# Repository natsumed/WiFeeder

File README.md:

# WiFeeder v2 — Project README

> **Wireless Automatic Cow Feeding System**  
> NRF24L01+ 2.4 GHz Communication | NUCLEO-L432KC | Raspberry Pi  

> **Status (2026-08-11):** Wiring MVP locked (PCA9685). **NRF VCC = 3.3 V** — Nucleo 5V (~4.8 V) permanently kills PA/LNA (SPI can still look OK). Firmware motor path is I2C PCA9685. Actuator hybrid PCB in [`pcb/`](pcb/). Pi host uses **JSON**. RF over-air still the bring-up gate (need **new** modules after the 5 V damage).

---

## Quick Navigation

| Document | Description |
|----------|-------------|
| [docs/wifeeder-v2-final-plan.md](./docs/wifeeder-v2-final-plan.md) | **Implementation plan** — pins, v1 port, phases, acceptance |
| [ARCHITECTURE.md](./ARCHITECTURE.md) | System architecture, state machines, data flow diagrams |
| [HARDWARE.md](./HARDWARE.md) | Pin mappings, wiring diagrams, power budget |
| [pcb/](./pcb/) | **Actuator hybrid PCB** (KiCad **6.0**) — PCA9685 + bucks on-board; Nucleo/IBT/NRF modules |
| [wiring/](./wiring/) | **Fritzing pack** — bench / no-PCB; `wifeeder-v2.fzz`, GX map |
| [PROTOCOL.md](./PROTOCOL.md) | NRF24L01+ communication protocol specification |
| [SOFTWARE.md](./SOFTWARE.md) | Code architecture, task model, class diagrams |
| [TESTING.md](./TESTING.md) | Test strategy, test cases, validation procedures |
| [DEPLOYMENT.md](./DEPLOYMENT.md) | Build, flash, and deployment instructions |
| [TROUBLESHOOTING.md](./TROUBLESHOOTING.md) | Common problems and solutions |
| [BILL_OF_MATERIALS.md](./BILL_OF_MATERIALS.md) | Complete materials list |

---

## System Overview

```mermaid
graph LR
    CLOUD[" Agpro Cloud"] <-->|"MQTT"| RPI[" Raspberry Pi"]
    RPI <-.->|"NRF24L01+<br/>2.4 GHz"| STM[" NUCLEO-L432KC"]
    STM --> RFID[" RFID Reader"]
    STM --> MOTOR[" Motors (2x)"]
    STM --> HX711[" Load Cell"]
```

WiFeeder v2 is a complete rewrite of the original CAN-bus-based cow feeding system, replacing the problematic wired communication with reliable NRF24L01+ wireless modules.

- **Cow approaches feeder** → RFID tag read
- **Tag sent over NRF24L01+** → Raspberry Pi controller
- **Diet calculation** → Feed command sent back
- **Motors dispense feed** → Encoders verify quantity
- **Consumption reported** → Agpro cloud via MQTT

---

## Repository Structure

```
wifeeder-v2/
├── README.md                          # This file
├── ARCHITECTURE.md                    # System architecture
├── HARDWARE.md                        # Hardware specs
├── PROTOCOL.md                        # Communication protocol
├── SOFTWARE.md                        # Software architecture
├── TESTING.md                         # Test plan
├── DEPLOYMENT.md                      # Deployment guide
├── TROUBLESHOOTING.md                 # Troubleshooting
├── BILL_OF_MATERIALS.md              # Materials list
│
├── stm32/                             # STM32 firmware
│   ├── Core/{Inc,Src}/               # Application code
│   ├── Drivers/                       # HAL & CMSIS
│   ├── Middlewares/                   # FreeRTOS
│   └── Config/                        # RTOS config
│
├── raspberry/                         # RPi host software
│   ├── src/                           # C++ source
│   ├── include/                       # C++ headers
│   ├── config/                        # JSON configs
│   └── tests/                         # GTest tests
│
├── pcb/                               # Actuator hybrid KiCad 8 carrier
├── wiring/                            # Fritzing bench pack
├── docs/                              # Additional docs
├── scripts/                           # Build & deploy
├── tests/                             # Integration tests
└── assets/                            # Images & diagrams
```

---

## Key Differences from v1

| Feature | v1 (CAN) | v2 (NRF24L01+) |
|---------|----------|-----------------|
| Communication | CAN bus (wired) | NRF24L01+ (wireless) |
| MCU | STM32L486ZGTx | NUCLEO-L432KC |
| Motor Driver | GTK08 | IBT-2 (BTS7960B) |
| Power | Direct 12V | Mini360 DC-DC Buck |
| Protocol | CAN frames (8B) | NRF packets (32B) |
| Database | JSON file (`wifeeder-data.json`) | SQLite (planned) |
| Range | Limited by cable | ~100m wireless |
| Cost per node | ~$15 (CAN parts) | ~$3 (NRF module) |

---

## Quick Start

### Prerequisites

- **Hardware**: NUCLEO-L432KC, NRF24L01+ x2, IBT-2, RFID reader, motors with encoders, Raspberry Pi
- **Software**: STM32CubeIDE, CMake 3.16+, GCC arm-none-eabi, g++ C++20
- **Pi Tools**: spidev / sysfs GPIO, libmosquitto (optional), JSON file DB

### Build STM32 Firmware

```bash
cd stm32
mkdir build && cd build
cmake .. -DCMAKE_TOOLCHAIN_FILE=../cmake/toolchain-arm-none-eabi.cmake
cmake --build . -j$(nproc)
# Flash: Connect Nucleo via USB, drag .bin to virtual drive
```

### Build Raspberry Pi Host

```bash
cd raspberry
mkdir build && cd build
cmake .. -DCMAKE_BUILD_TYPE=Release
cmake --build . -j$(nproc)
# Install: sudo cmake --install .
```

### Configure & Run

```bash
# On Pi:
sudo systemctl enable wifeeder-v2
sudo systemctl start wifeeder-v2

# Monitor:
journalctl -u wifeeder-v2 -f

# Check NRF communication:
sudo candump nrf  # (uses virtual CAN interface to monitor NRF messages)
```

---

## Communication Flow

```mermaid
sequenceDiagram
    participant Cow as 
    participant STM32 as STM32
    participant RPi as RPi
    participant Cloud as  Cloud

    loop Every 5s
        STM32->>RPi: STATUS (heartbeat)
        RPi->>STM32: ACK
    end

    Cow->>STM32: RFID tag read
    STM32->>RPi: RFID_TAG
    RPi->>RPi: Lookup diet
    RPi->>STM32: FEED_CMD (revolutions)
    STM32->>STM32: Dispense feed
    STM32->>RPi: FEED_DONE (actual)
    RPi->>Cloud: Publish via MQTT
```

---

## License

Proprietary — CodinTek © 2024

## Support

For questions or issues, see [TROUBLESHOOTING.md](./TROUBLESHOOTING.md) or contact the development team.

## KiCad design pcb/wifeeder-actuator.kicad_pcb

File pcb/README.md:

# WiFeeder actuator carrier (hybrid, spin 1)

KiCad **6.0** project (matches this machine): [`wifeeder-actuator.kicad_pro`](wifeeder-actuator.kicad_pro)

Replaces the Fritzing breadboard, PCA9685 breakout, Mini360, and jumper harness.
Firmware pins are unchanged — see [`../stm32/Core/Inc/board.h`](../stm32/Core/Inc/board.h) and
[`../wiring/CONNECTOR_MAP.md`](../wiring/CONNECTOR_MAP.md).

| On this PCB | Plug-in modules | Off-board |
|-------------|-----------------|-----------|
| PCA9685 + passives | NUCLEO-L432KC | Raspberry Pi + NRF |
| Fixed 5 V + 3.3 V bucks | IBT-2 (BTS7960) | PN01007BRKT + GTS06 |
| Enc / I2C pull-ups, fuse, TVS, P-FET | NRF24 + AM1117 (2×4) | 12 V pack |
| Screw / JST connectors | Mini360 **DNP fallback only** | — |

**Do not** chip-down STM32, BTS7960, or nRF24 on this spin.

## Open / regenerate

```bash
# Open in KiCad 6.0 (installed as /usr/bin/kicad)
kicad pcb/wifeeder-actuator.kicad_pro

# After open: PCB editor → B (fill zones) → Inspect → Design Rules Checker
# Schematic: Inspect → Electrical Rules Checker

# Regenerate schematic + placement (no copper — does NOT route)
python3 pcb/tools/generate_project.py
python3 pcb/tools/route_pcb.py      # power + signal routing
python3 pcb/tools/verify_pcb.py     # KiCad connectivity (unconnected must be 0)
python3 pcb/tools/export_fab.py     # zone fill + gerbers
python3 pcb/tools/audit_pcb.py      # pad-to-trace check
```

Fritzing remains the **no-PCB bench** pack under [`../wiring/`](../wiring/).

## Power (read before first apply)

1. No modules seated. Apply 12 V to **TB1**. Measure **TP5V ≈ 5.00 V**, **TP3V3 ≈ 3.30 V**.
2. Seat Nucleo with **USB unplugged** (carrier feeds **3V3 → Nucleo 3V3**).
3. Seat NRF adapter: **VCC is 5 V** (not 3.3 V).
4. Seat IBT-2. Wire **TB2** (12V_SAFE / GND) to IBT **B+ / B−** with short 16 AWG (module has no underside power pins). Motor: IBT **M+/M−** and/or **TB3**.
5. Encoder on **TB4** (5 V VCC, 3.3 V pull-ups on A/B).

Mini360 (`J_MINI`) is **do not populate** unless the AP63203 is omitted and `SJ_MINI` is closed.

## Sheets

| File | Contents |
|------|----------|
| `wifeeder-actuator.kicad_sch` | Root / hierarchy |
| `power.kicad_sch` | 12 V protect, 5 V / 3.3 V bucks, Mini360 DNP |
| `mcu.kicad_sch` | Nucleo-32 sockets, NRF, encoder, RFID/HX711 DNP |
| `pca.kicad_sch` | PCA9685 chip-down |
| `ibt.kicad_sch` | IBT-2 logic + power screws |
| `connectors.kicad_sch` | Mechanical notes / mounting |

Pinouts: [`CONNECTORS.md`](CONNECTORS.md).

## Fab

- 2-layer, 1.6 mm, 2 oz Cu preferred, 100×150 mm, ENIG or HASL
- Gerbers: [`fab/`](fab/)
- Keepout: no 12 V under NRF antenna (top-right)

## Bring-up

1. Rails only (above)
2. Nucleo LED blink
3. PCA ACK `0x40`
4. [`../tests/04-motor`](../tests/04-motor/)
5. NRF tests 10 then 09, CH **76**, antennas, ≥10 cm
6. Encoder **2400** counts/rev

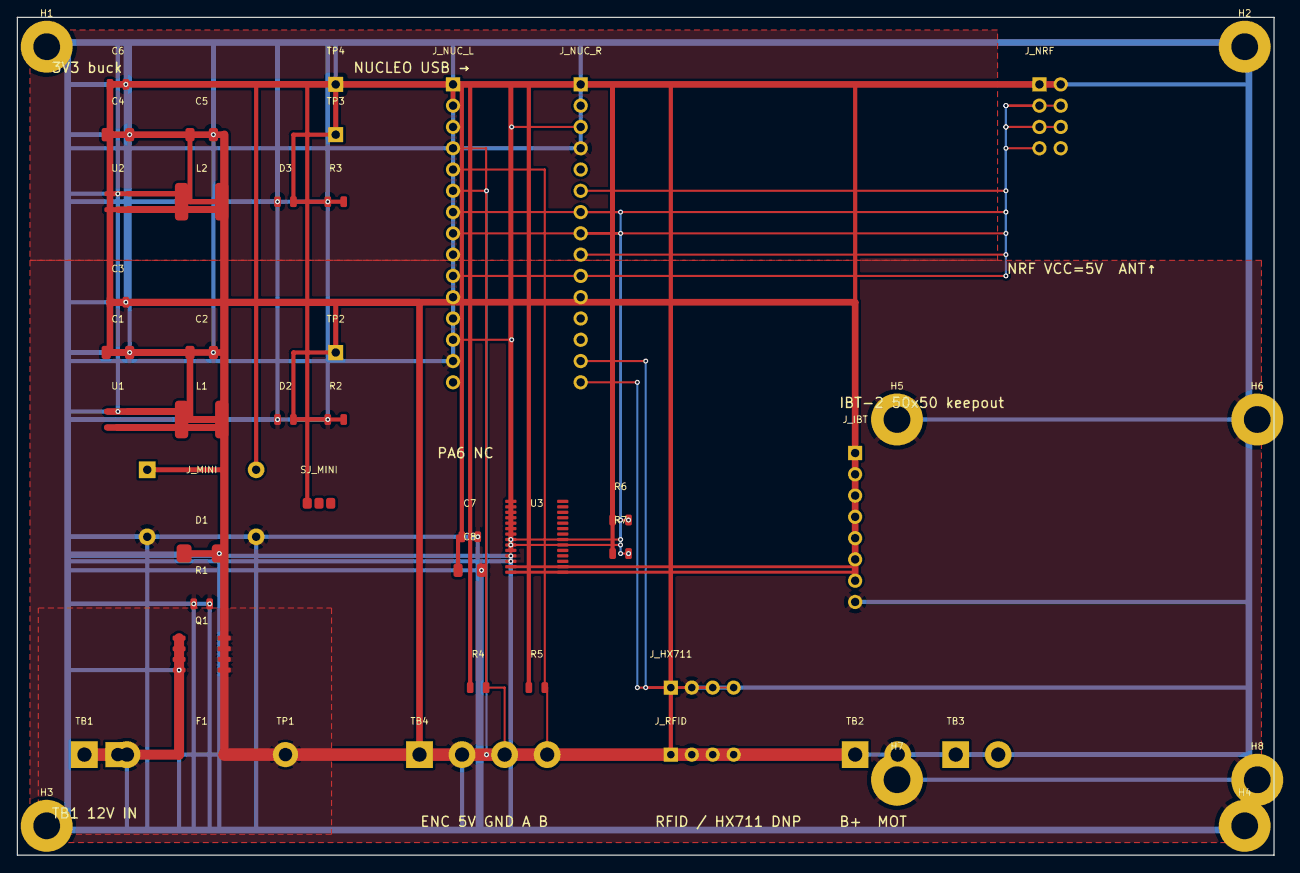
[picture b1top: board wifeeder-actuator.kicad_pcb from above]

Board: 2 copper layers, 150.0 x 100.0 mm, 49 parts (0 on the bottom side), 20 nets.

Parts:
C1, C4, C8: 10uF; C_1206
C2, C5: 22uF; C_1206
C3, C6, C7: 100n; C_0805
D1: SMAJ15A; SMA
D2: 5V; LED_0805
D3: 3V3; LED_0805
F1: 10A; Fuse_5x20
H1, H2, H3, H4: M3; MountingHole_M3
H5, H6, H7, H8: IBT; MountingHole_M3
J_HX711: HX711; JST_XH_04
J_IBT: IBT logic; PinSocket_1x08
J_MINI: DNP; Mini360
J_NRF: NRF 5V; PinSocket_2x04
J_NUC_L: CN3; PinSocket_1x15
J_NUC_R: CN4; PinSocket_1x15
J_RFID: RFID; JST_XH_04
L1, L2: 4.7uH; L_6x6
Q1: AO4407A; SOIC-8
R1: 100k; R_0805
R2, R3: 1k; R_0805
R4, R5, R6, R7: 4.7k; R_0805
SJ_MINI: OPEN; SolderJumper_3
TB1: 12V_IN; Terminal_2
TB2: IBT B+; Terminal_2
TB3: MOTOR; Terminal_2
TB4: ENC; Terminal_4
TP1: 12V; TestPoint
TP2: 5V; TestPoint
TP3: 3V3; TestPoint
TP4: GND; TestPoint
U1: AP63205; SOT23-6
U2: AP63203; SOT23-6
U3: PCA9685; TSSOP-28

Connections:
3V3: C5.1, C6.1, C7.1, C8.1, D3.2, J_HX711.1, J_IBT.3, J_IBT.4, J_MINI.3, J_NUC_L.2, L2.1, L2.2, R3.2, R4.1, R5.1, R6.1, R7.1, SJ_MINI.1, TP3.1, U2.1, U2.3, U2.6, U3.10
5V: C2.1, C3.1, D2.2, J_IBT.7, J_NRF.2, J_RFID.1, L1.1, L1.2, R2.2, TB4.1, TP2.1, U1.1, U1.3, U1.6
12V_IN: F1.1, Q1.1, Q1.2, Q1.3, TB1.1
12V_SAFE: C1.1, C4.1, D1.1, F1.2, J_MINI.1, Q1.5, Q1.6, Q1.7, Q1.8, TB2.1, TP1.1, U1.4, U1.5, U2.4, U2.5
ENC_A: J_NUC_L.4, R4.2, TB4.3
ENC_B: J_NUC_L.5, R5.2, TB4.4
GND: C1.2, C2.2, C3.2, C4.2, C5.2, C6.2, C7.2, C8.2, D1.2, D2.1, D3.1, J_HX711.2, J_IBT.8, J_MINI.2, J_MINI.4, J_NRF.1, J_NUC_L.14, J_NUC_R.4, J_RFID.2, Q1.4, R1.1, R1.2, R2.1, R3.1, TB1.2, TB2.2, TB4.2, TP4.1, U1.2, U2.2, U3.11, U3.12
HX711_DOUT: J_HX711.3, J_NUC_R.15
HX711_SCK: J_HX711.4, J_NUC_R.14
I2C_SCL: J_NUC_R.8, R6.2, U3.8
I2C_SDA: J_NUC_R.7, R7.2, U3.9
NRF_CE: J_NRF.3, J_NUC_R.6
NRF_CSN: J_NRF.4, J_NUC_L.7
NRF_MISO: J_NRF.7, J_NUC_R.9
NRF_MOSI: J_NRF.6, J_NUC_L.10
NRF_SCK: J_NRF.5, J_NUC_L.8
NUC_NRST: J_NUC_L.13, J_NUC_R.3
PWM0: J_IBT.1, U3.13
PWM1: J_IBT.2, U3.14
RFID_RX: J_NUC_L.6, J_RFID.3

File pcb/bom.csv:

Item,Qty,Value,Package,Ref,Notes
1,1,NUCLEO-L432KC,Nano 15+15 socket,J_NUC_L J_NUC_R,Module — do not chip-down
2,1,IBT-2 BTS7960,50x50 module,J_IBT TB2,Logic socket + B+/B- screws
3,1,NRF24 AM1117 adapter,2x4 2.54,J_NRF,VCC=5V
4,1,PCA9685,TSSOP-28,U3,Addr 0x40 OE=GND
5,1,AP63205,SOT-23-6,U1,Fixed 5V ~2A
6,1,AP63203,SOT-23-6,U2,Fixed 3.3V ~1A
7,2,4.7uH 3A,6x6,L1 L2,
8,1,AO4407A,SOIC-8,Q1,Reverse-polarity P-FET
9,1,SMAJ15A,SMA,D1,TVS 15V
10,1,10A 5x20 fuse,clips,F1,
11,4,10uF 25V,1206,C1 C4 C8,
12,2,22uF 16V,1206,C2 C5,
13,4,100nF,0805,C3 C6 C7,
14,2,4.7k I2C,0805,R6 R7,
15,2,4.7k Enc,0805,R4 R5,
16,1,100k,0805,R1,Q1 gate
17,2,1k,0805,R2 R3,LED
18,2,LED green,0805,D2 D3,5V / 3V3
19,3,Terminal 5.08 2p,,TB1 TB2 TB3,12V / IBT / motor
20,1,Terminal 5.08 4p,,TB4,Encoder GX fly-wire
21,2,JST-XH-4,DNP,J_RFID J_HX711,Unpopulated MVP
22,1,Mini360,DNP,J_MINI,Only if U2 omitted
23,8,M3 hole,,H1-H8,Board + IBT
24,0,Mini360 stuffed,,—,Default not fitted

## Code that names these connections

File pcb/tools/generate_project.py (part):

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    for i, net, shp in cn3:
        y = 110 + h - (i - 1) * 2.54
        m.glabel(net, 35, y, 180, shp if shp != "passive" else "passive")
        if net in ("PA6_NC", "AREF", "NUC_5V", "NUC_VIN", "PA2_VCP", "D13_PB3", "NUC_NRST"):
            m.no_connect(42.38, y)

    cn4 = [
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    for i, net, shp in cn4:
        y = 110 + h - (i - 1) * 2.54
        m.glabel(net, 135, y, 0, shp)
        if net in ("PA9", "PA10", "PA12", "PC14", "PC15", "PA8", "PA11", "NUC_NRST"):
            m.no_connect(127.62, y)
        else:
            m.wire(127.62, y, 135, y)
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    m.text("J_NRF: 1 GND  2 VCC=5V  3 CE  4 CSN  5 SCK  6 MOSI  7 MISO  8 IRQ nc", 165, 165, 1.4)
    m.glabel("GND", 185, 148.89, 180, "input")
    m.glabel("5V", 185, 146.35, 180, "input")
    m.glabel("NRF_CE", 185, 143.81, 180, "input")
    m.glabel("NRF_CSN", 185, 141.27, 180, "input")
    m.glabel("NRF_SCK", 185, 138.73, 180, "input")
    m.glabel("NRF_MOSI", 185, 136.19, 180, "input")
    m.glabel("NRF_MISO", 185, 133.65, 180, "output")
    m.no_connect(192.38, 131.11)  # IRQ

    m.symbol("Conn_01x04", "TB4", "ENC GX fly", 50, 40, "wifeeder:Terminal_4", ["1", "2", "3", "4"])
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    m.text("TB4: 1=5V  2=GND  3=A  4=B   pull-ups R4/R5 to 3V3 (not 5V)", 20, 22, 1.5)
    m.glabel("5V", 35, 43.81, 180, "input")
    m.glabel("GND", 35, 41.27, 180, "input")
    m.glabel("ENC_A", 35, 38.73, 180, "bidirectional")
    m.glabel("ENC_B", 35, 36.19, 180, "bidirectional")
    m.glabel("3V3", 80, 58, 90, "input")
    m.glabel("3V3", 200, 100, 90, "input")
    m.glabel("I2C_SCL", 200, 82, 270, "bidirectional")
    m.glabel("I2C_SDA", 215, 82, 270, "bidirectional")

    m.symbol("Conn_01x04", "J_RFID", "RFID DNP", 130, 40, "wifeeder:JST_XH_04", ["1", "2", "3", "4"])
    m.symbol("Conn_01x04", "J_HX711", "HX711 DNP", 180, 40, "wifeeder:JST_XH_04", ["1", "2", "3", "4"])
    m.symbol("SolderJumper_3", "SJ_RFID_V", "3V3/5V", 130, 18, "wifeeder:SolderJumper_3", ["1", "2", "3"])
    m.text("J_RFID: 1 VCC 2 GND 3 RX←PA3 4 NC    J_HX711: 1 3V3 2 GND 3 DOUT 4 SCK", 20, 16, 1.4)
    m.glabel("RFID_RX", 115, 38.73, 180, "input")
    m.glabel("GND", 115, 41.27, 180, "input")
    m.glabel("HX711_DOUT", 165, 38.73, 180, "output")
    m.glabel("HX711_SCK", 165, 36.19, 180, "input")
    m.glabel("3V3", 165, 43.81, 180, "input")
    m.glabel("GND", 165, 41.27, 180, "input")

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             [str(i) for i in range(1, 29)])
    c.symbol("C", "C7", "100n", 40, 80, "wifeeder:C_0805", ["1", "2"])
    c.symbol("C", "C8", "10uF", 40, 65, "wifeeder:C_1206", ["1", "2"])
    c.glabel("I2C_SCL", 55, 107.46, 180, "bidirectional")
    c.glabel("I2C_SDA", 55, 104.92, 180, "bidirectional")
    c.glabel("3V3", 55, 102.38, 180, "input")
    c.glabel("GND", 55, 99.84, 180, "input")
    c.glabel("PWM0", 105, 125.24, 0, "output")
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    nuc_x, nuc_y = 52.0, 8.0
    cn3_nets = [
        "D13_PB3", "3V3", "AREF", "ENC_A", "ENC_B", "RFID_RX", "NRF_CSN",
        "NRF_SCK", "PA6_NC", "NRF_MOSI", "PA2_VCP", "NUC_5V", "NUC_NRST", "GND", "NUC_VIN",
    ]
    cn4_nets = [
        "PA9", "PA10", "NUC_NRST", "GND", "PA12", "NRF_CE", "I2C_SDA",
        "I2C_SCL", "NRF_MISO", "PC14", "PC15", "PA8", "PA11", "HX711_SCK", "HX711_DOUT",
    ]
    b.fp("wifeeder:PinSocket_1x15", "J_NUC_L", "CN3", nuc_x, nuc_y, sock_1x(15, cn3_nets))
    b.fp("wifeeder:PinSocket_1x15", "J_NUC_R", "CN4", nuc_x + 15.24, nuc_y, sock_1x(15, cn4_nets))
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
